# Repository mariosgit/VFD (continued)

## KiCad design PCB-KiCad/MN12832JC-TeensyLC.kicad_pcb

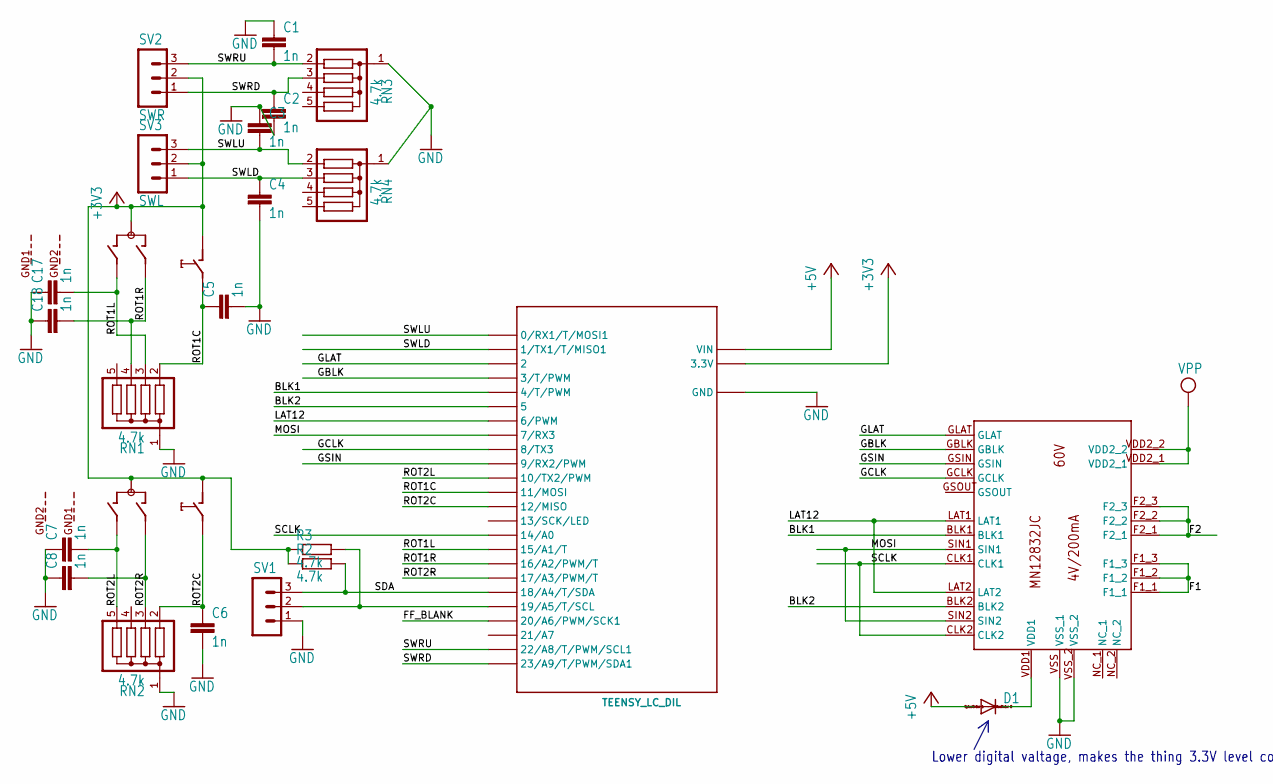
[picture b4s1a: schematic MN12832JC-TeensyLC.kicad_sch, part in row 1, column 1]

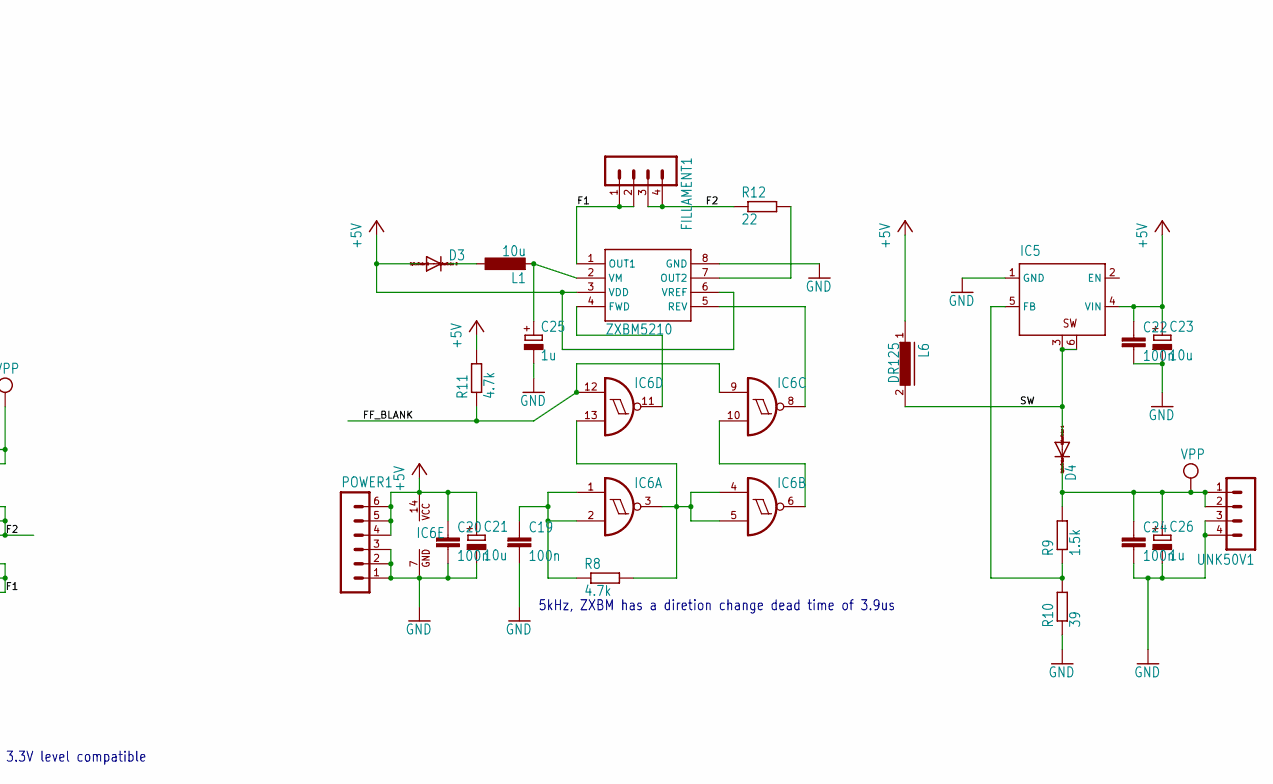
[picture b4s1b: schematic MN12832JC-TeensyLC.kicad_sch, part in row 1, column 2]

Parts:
C1, C2, C3, C4, C5, C6, C7, C8, C17, C18: 1n; C1206
C19, C20, C22, C24: 100n; C1206
C21, C23: 10u; 153CLV-0807
C25, C26: 1u; 153CLV-0505
D1, D3, D4: DIODE-SMB; SMB
FILLAMENT1: MA04-1
IC4: ZXBM5210; SO8
IC5: XL6009; TO263-5
IC6: 74132D; SO14
L1: 10u; L1812
L6: DR125
POWER1: MA06-1
R2, R3, R8, R11: 4.7k; R1206
R9: 1.5k; R1206
R10: 39; R1206
R12: 22; 0411_15
RN1, RN2, RN3, RN4: 4.7k; SIL5
SV1: MA03-1
SV2: SWR; MA03-1
SV3: SWL; MA03-1
SW3, SW4: EC12E_SW; ALPS_EC12E_SW
U$1: MN12832JC
U$3: TEENSY_LC_DIL; TEENSY_3.0-3.2&LC_DIL
UNK50V1: MA04-1

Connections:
+3V3: R2.1, R3.1, SV2.2, SV3.2, SW3.C, SW3.D (1), SW4.C, SW4.D (1), U$3.3.3V
+5V: C20.1, C21.+, C22.1, C23.+, D1.A, D3.A, IC4.3 (VDD), IC4.6 (VREF), IC5.4 (VIN), IC6.14 (VCC), L6.1, POWER1.4, POWER1.5, POWER1.6, R11.2, U$3.VIN
/BLK1: U$1.BLK1, U$3.4 (4/T/PWM)
/BLK2: U$1.BLK2, U$3.5
/F1: FILLAMENT1.1, FILLAMENT1.2, IC4.1 (OUT1), U$1.F1_1, U$1.F1_2, U$1.F1_3
/F2: FILLAMENT1.3, FILLAMENT1.4, R12.1, U$1.F2_1, U$1.F2_2, U$1.F2_3
/FF_BLANK: IC6.9 (I0), IC6.12 (I0), R11.1, U$3.20/A6 (20/A6/PWM/SCK1)
/GBLK: U$1.GBLK, U$3.3 (3/T/PWM)
/GCLK: U$1.GCLK, U$3.8 (8/TX3)
/GLAT: U$1.GLAT, U$3.2
/GSIN: U$1.GSIN, U$3.9 (9/RX2/PWM)
/LAT12: U$1.LAT1, U$1.LAT2, U$3.6 (6/PWM)
/MOSI: U$1.SIN1, U$1.SIN2, U$3.7 (7/RX3)
/ROT1C: C5.1, RN1.2, SW3.E (2), U$3.11 (11/MOSI)
/ROT1L: C17.2, RN1.3, SW3.B, U$3.15/A1 (15/A1/T)
/ROT1R: C18.2, RN1.4, SW3.A, U$3.16/A2 (16/A2/PWM/T)
/ROT2C: C6.1, RN2.2, SW4.E (2), U$3.12 (12/MISO)
/ROT2L: C7.2, RN2.5, SW4.B, U$3.10 (10/TX2/PWM)
/ROT2R: C8.2, RN2.3, SW4.A, U$3.17/A3 (17/A3/PWM/T)
/SCLK: U$1.CLK1, U$1.CLK2, U$3.14/A0
/SDA: R2.2, SV1.3, U$3.18/A4 (18/A4/T/SDA)
/SW: D4.A, IC5.3 (SW), IC5.6 (SW@1), L6.2
/SWLD: C4.1, RN4.3, SV3.1, U$3.1 (1/TX1/T/MISO1)
/SWLU: C3.2, RN4.2, SV3.3, U$3.0 (0/RX1/T/MOSI1)
/SWRD: C2.1, RN3.3, SV2.1, U$3.23/A9 (23/A9/T/PWM/SDA1)
/SWRU: C1.2, RN3.2, SV2.3, U$3.22/A8 (22/A8/T/PWM/SCL1)
GND: C1.1, C2.2, C3.1, C4.2, C5.2, C6.2, C7.1, C8.1, C17.1, C18.1, C19.2, C20.2, C21.-, C22.2, C23.-, C24.2, C25.-, C26.-, IC4.8 (GND), IC5.1 (GND), IC6.7 (GND), POWER1.1, POWER1.2, POWER1.3, R10.1, RN1.1, RN2.1, RN3.1, RN4.1, SV1.1, U$1.VSS (VSS_1), U$1.VSS_2, U$3.AGND (GND), U$3.GND, UNK50V1.3, UNK50V1.4
unnamed: D1.C, U$1.VDD1
unnamed: D3.C, L1.1
unnamed: IC4.4 (FWD), IC6.11 (O)
unnamed: IC4.7 (OUT2), R12.2
unnamed: IC4.5 (REV), IC6.8 (O)
unnamed: C25.+, IC4.2 (VM), L1.2
unnamed: IC5.5 (FB), R9.1, R10.2
unnamed: C19.1, IC6.1 (I0), IC6.2 (I1), R8.1
unnamed: IC6.3 (O), IC6.4 (I0), IC6.5 (I1), IC6.13 (I1), R8.2
unnamed: IC6.6 (O), IC6.10 (I1)
unnamed: R3.2, SV1.2, U$3.19/A5 (19/A5/T/SCL)
VPP: C24.1, C26.+, D4.C, R9.2, U$1.VDD2_1, U$1.VDD2_2, UNK50V1.1, UNK50V1.2

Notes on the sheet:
5kHz, ZXBM has a diretion change dead time of 3.9us ~{}
Lower digital valtage, makes the thing 3.3V level compatible

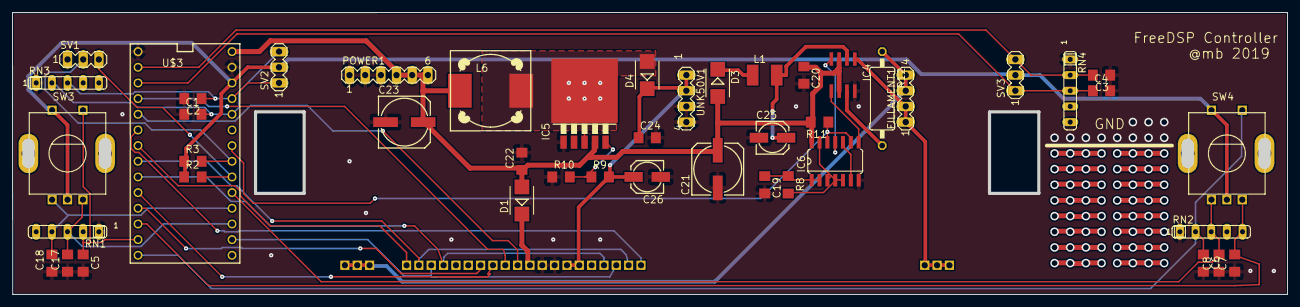
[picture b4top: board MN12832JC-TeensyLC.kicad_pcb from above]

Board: 2 copper layers, 206.7 x 45.7 mm, 47 parts (1 on the bottom side), 39 nets.

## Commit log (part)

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2018-04-25 Initial test program for TPIC6b595.
2018-04-25 Copy of the TPIC code for NEC FIP20D9X
2018-04-26 Update README.md
    Added instructable link.
2018-10-01 A bit more detail..
2018-10-28 It works.
2018-10-28 added image
2018-10-28 moved image
2018-10-28 Added Log lib, used here and there.
2018-10-28 Bit more Doc.
2018-10-28 Optimized, shorter interrupt, brighter display.
2019-01-07 Added some drawing demo code.
2019-01-08 First Attempt to use a STM32F1x. Experimenting with a MN12864.
2019-01-08 Ignore .vscode.
2019-11-10 Added PCBs.
2019-11-10 working on BOM
2019-11-19 Larger Drills for Display
2019-11-19 locked proto area, will not ripup and disappear
2019-11-20 minor stuff
2019-11-20 fixed Up Converter R9/R10 twist, adjusted values for 50V
2019-11-21 set PWM pin to high for the new board.
2019-11-22 Added Voltage drop diode for Vdd1, lowered Fillament frequency to avoid off time
2019-11-26 adapted for use with the AMP1, inital working version
2019-12-01 Rearanged in a bit more Arduino library style.
2019-12-01 sorted out example code vs. Panel code.
2019-12-04 added FreeDSP controller. Reads Levels. Sets Volume.
2019-12-04 LevelMeter+Volume
2019-12-04 Typo, Libpath
2019-12-04 updated readme...
2019-12-04 nicer
2019-12-04 todo list...
2019-12-04 more todo
2019-12-09 Waiting for I2C silence after boot.
2024-01-08 Freedom for makers !
2024-01-08 kicad ignore update.
2024-01-10 Progress on GP1294 board..
2024-01-15 GP1294 progress..
2024-01-16 GP1294 progress...
2024-01-18 GP1294...
2024-01-18 GP1294 more progress...
2024-01-21 more progress
2024-01-22 GP12.. better case and stuff
2024-01-23 ATtiny software for input control.
2024-01-29 GP1294 evolves
2024-01-31 Starting GP1294 software
2024-01-31 GP1294 stuff..
2024-02-01 Added SRC.
2024-02-01 grummel
2024-02-01 Fixed merge issues.
2024-02-02 nix.
2024-02-08 Added OLED 5.5" option
2024-02-09 Upgraded Power circuit.
2024-02-09 Added test code for GP1294
2024-02-12 Added Debounce Caps and stuff.
2024-02-15 README updated, restructuring..
2024-02-15 Rearranged into PlatformIO project.
2024-02-15 missing peaces..
2024-02-15 Experiments with MN12832L...
2024-02-16 Progress...
2024-02-16 Added Odd/Even buffers.
2024-02-16 Breakpoint, looking better, but only one gate active.
2024-02-16 Breakpoint, ok, just the seams...
2024-02-16 Nicer Demo
2024-02-16 Somewhat useable...
2024-02-19 Replaced dualbuffer with masking.
2024-02-19 Added doubl buffer.
2024-02-19 Runs with serial 1->2 chain.
2024-02-19 breakpoint, shift out 2x for serial in chain.
2024-02-19 Added greyscale.
2024-02-19 README merge.
2024-02-19 Moved MN12832L to own repo.
2024-02-19 still..
2024-02-19 Updated README.
2024-02-21 Progress with MN12832L...
2024-02-22 Compile on STM32
2024-02-22 Working on MN12864K...
2024-02-23 Experiments with MN12864K...
2024-02-23 Can change build example by .env file.
2024-02-23 Not much..
2024-02-23 Cleaned up readme.
2024-02-23 Stuff
2024-02-23 Fixing git..
2024-02-23 Readded subrepo.
2024-02-23 Readded subrepo 2
2024-02-23 Progress with MN12864K.
2024-02-26 drawFastHLine...
2024-02-26 Cleanup.
2024-02-26 Better.
2024-02-28 Added lib/font and example under MN12832L
2024-03-05 PCB: TestPin must pull up with 100k.
2024-03-05 More GP1294 experiments and stuff.
2024-03-06 Nicer Demo.
2024-03-06 hkgkgk
2024-03-07 GP1294 board, added light and remote sensors.
2024-03-07 Fixed merge fail.
2024-03-12 input test..
2024-03-14 Fixed i2c..
2024-03-27 Some silkscreen fixes.
2024-03-27 Input: Minifix
2024-05-23 Checks and Firmware after 1st build.
2024-05-27 Removed confusing stuff
2024-05-27 Trouble with submodules...
2024-06-10 Threads for all.
2024-06-19 Updated case for 3d print.
2024-08-30 GP1291 fixes, removed input mcu, added SRCs.
2024-08-30 Updated README todo list.
2024-09-18 Added new HUI panel with MN12832L
2024-09-18 Updated README..
2024-09-29 Beauty fixes
2024-10-01 tests with new MN12832L panel.
2024-10-01 Added FreeDSPControllerMN12832L
2024-10-02 More stuff for MN12832L-panel
2024-10-05 Going back to teensylc.
2024-10-05 Some fixes..
2024-10-05 More fixes
2024-10-05 Case update.
2024-10-06 More Case
2024-10-10 Added distortion encoder.
2024-10-11 Moved some stuff to SigmaDSP lib.
2024-10-11 Moved more stuff to SigmaDSP lib
2024-10-14 Tested TeensyAudio biquad calc, it's useable.
2024-10-15 FreeDSPCtlMN12832L as good as done.
2024-10-15 Minor fixes
2024-10-17 Added Crossover and some stuff.
2024-10-17 Added log of crossover params.
2024-10-18 Changed some preset dsp values, fixed input?
2024-10-21 EQ and stuff for W3 fast chassis.
2024-10-30 temp..
2024-10-30 Checked, fixed timing.
2024-10-31 Upgraded to 8 band EQ.
2024-10-31 Added some peak checkers and compression.
2024-10-31 Reading the readback stuff....
2024-11-02 Changed EQ and Speki to 9 bands.
